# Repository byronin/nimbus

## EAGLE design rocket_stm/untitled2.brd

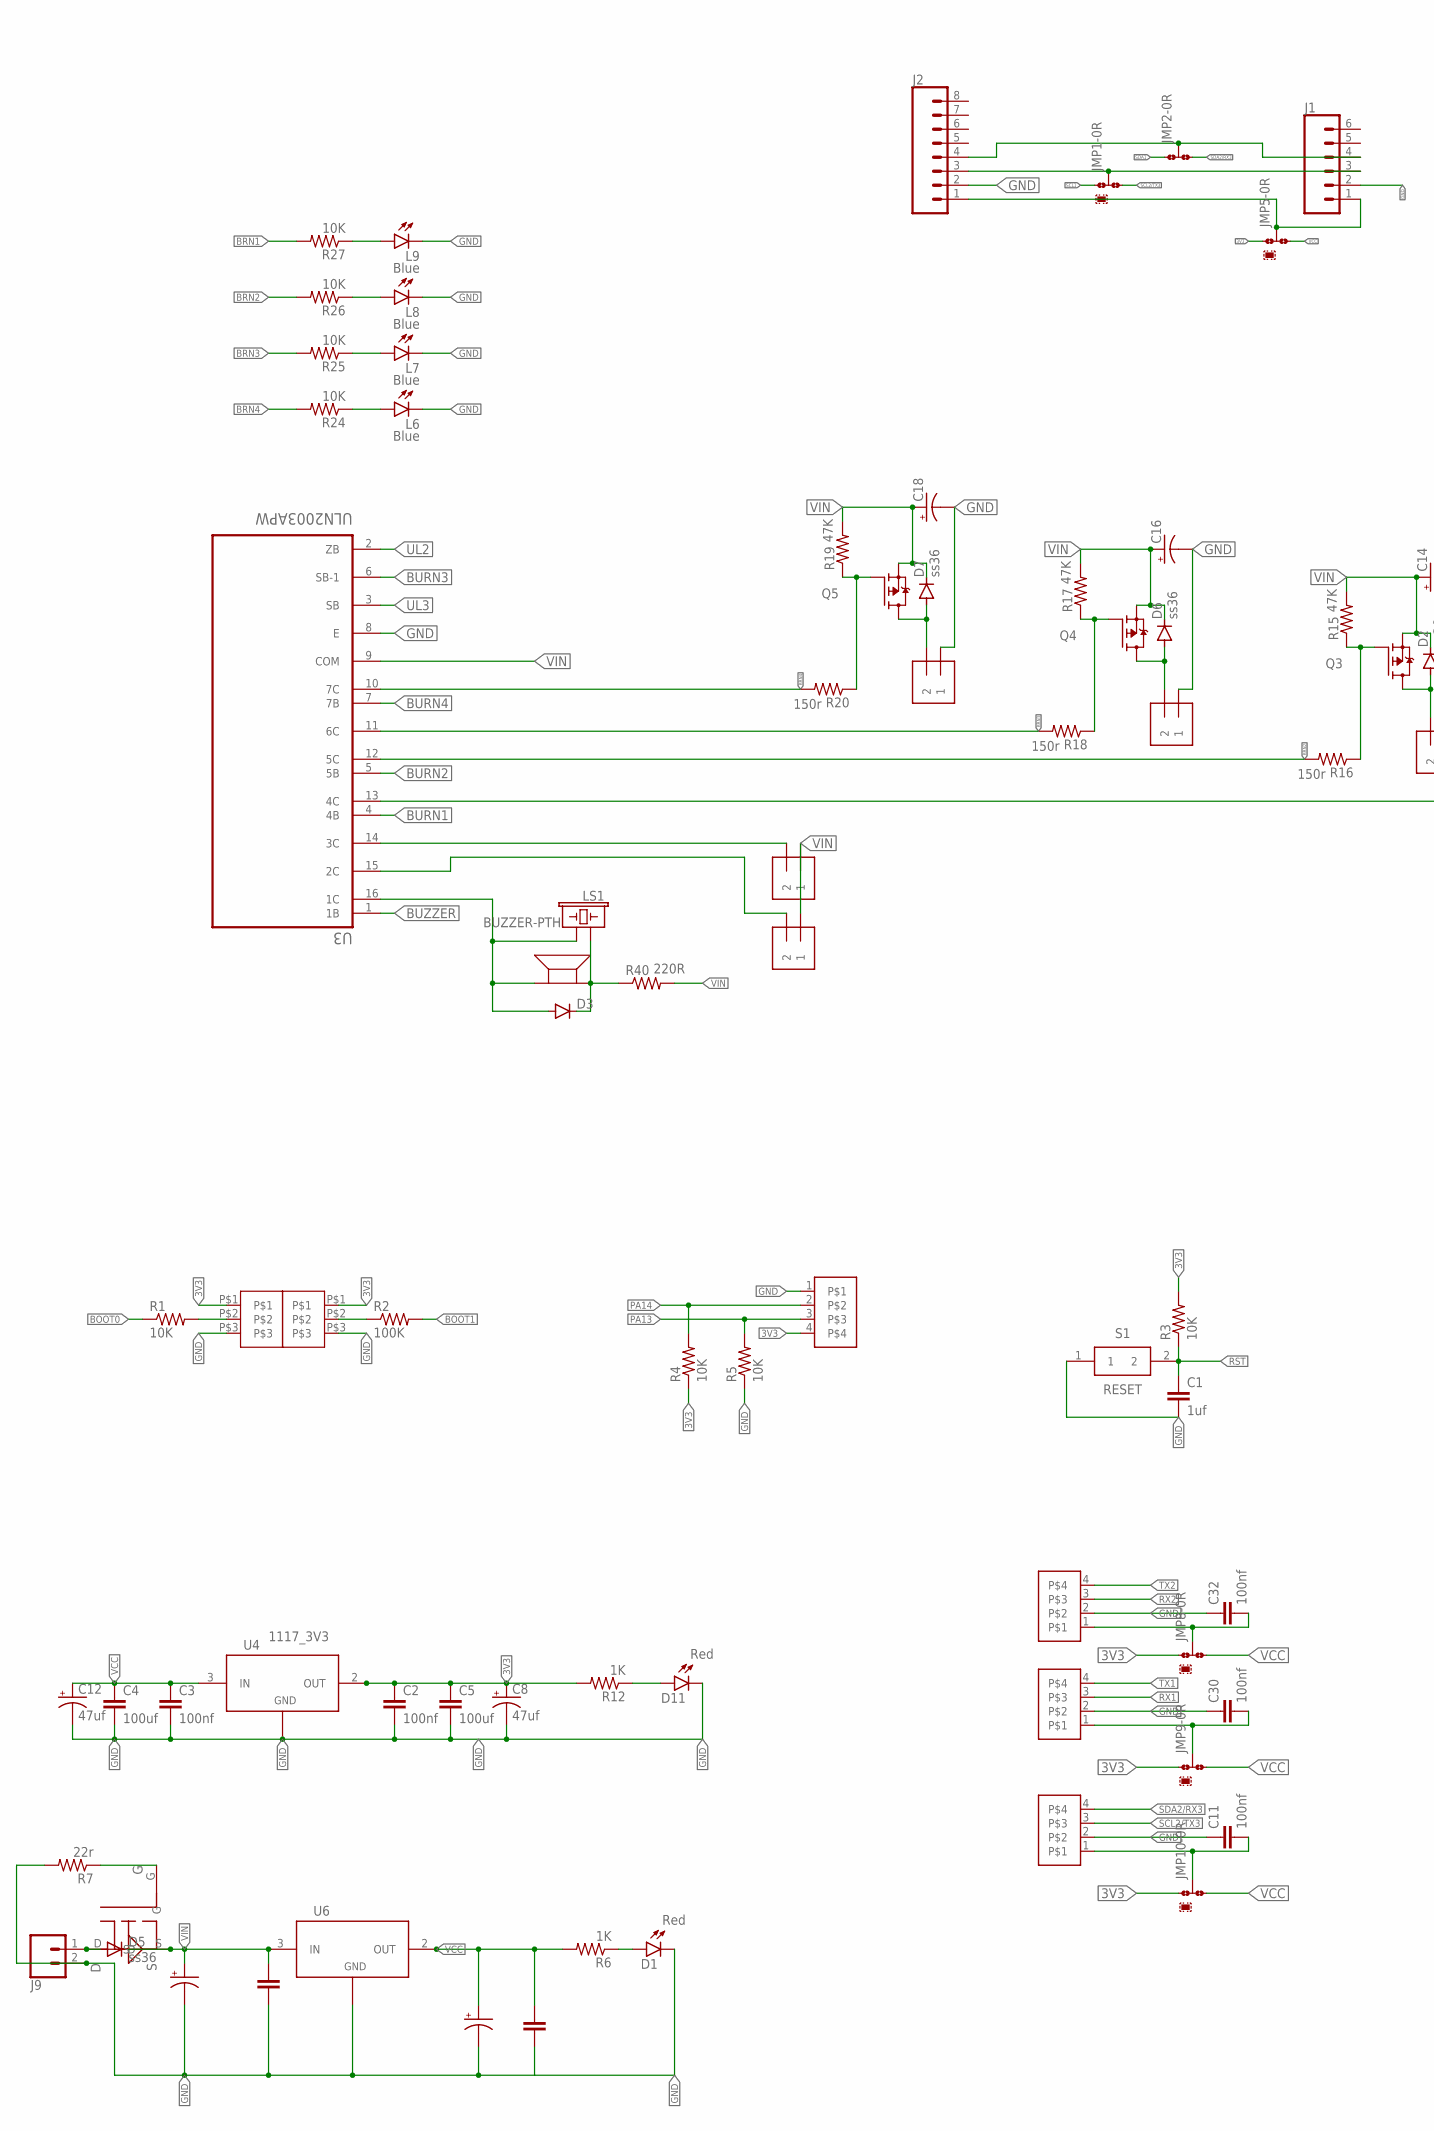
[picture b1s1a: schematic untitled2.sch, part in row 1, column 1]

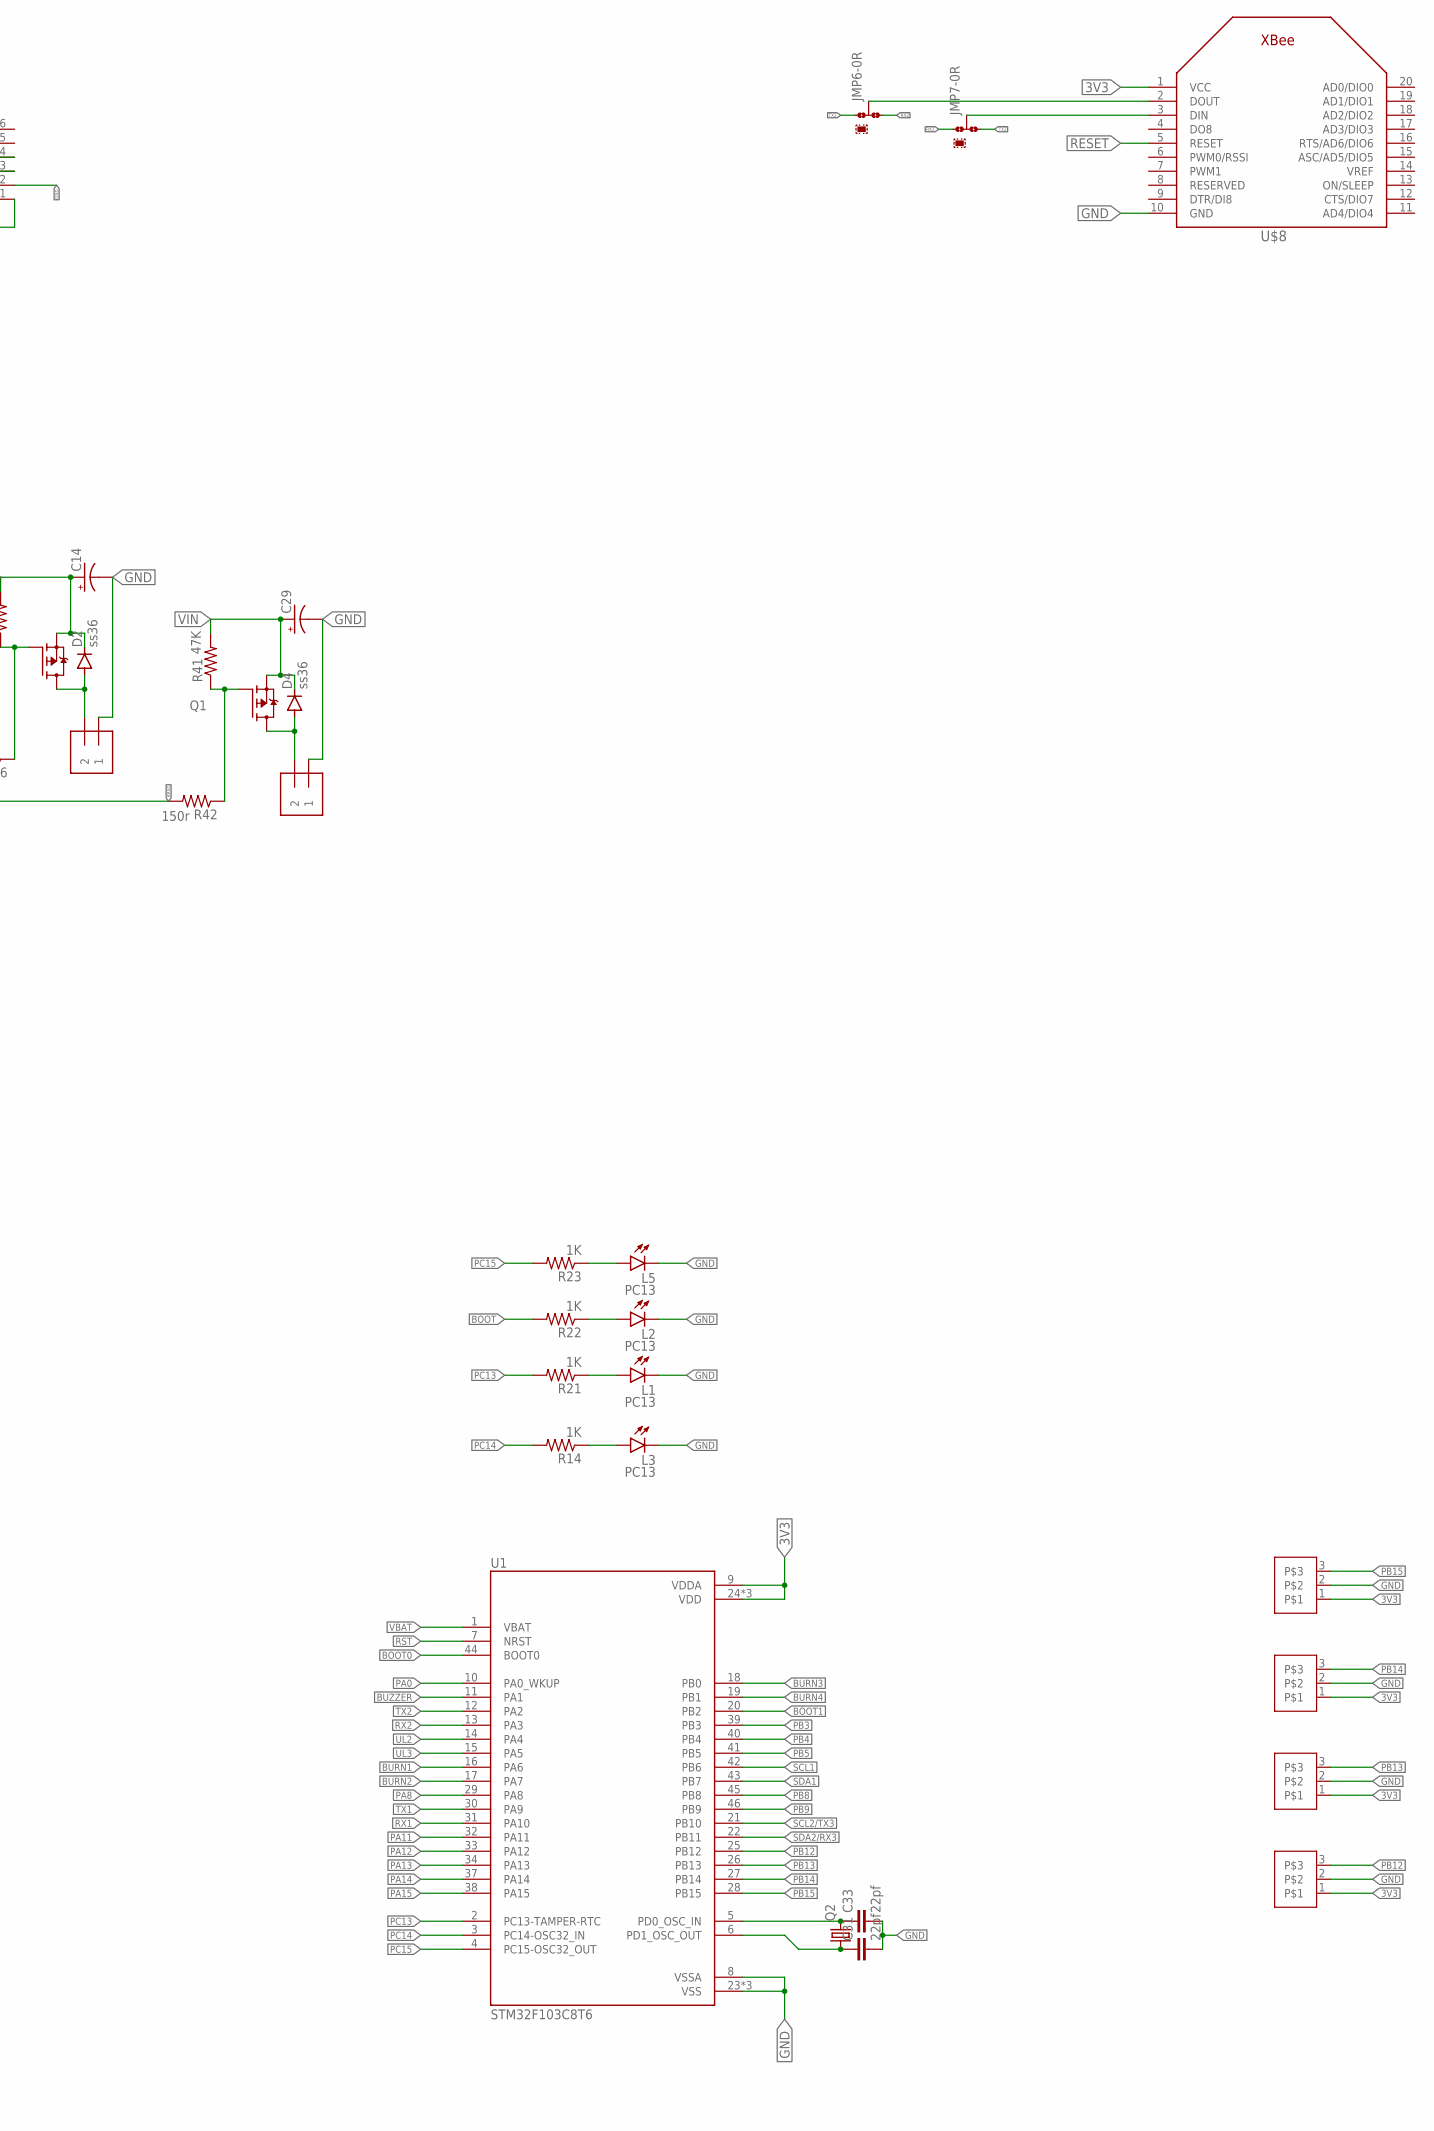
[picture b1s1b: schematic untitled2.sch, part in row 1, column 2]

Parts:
C1: 1uf; C0603
C2, C3, C6, C9, C11, C30, C32: 100nf; C0603
C4, C5: 100uf; C1210
C7, C10: 100uf; PANASONIC_D
C8, C12: 47uf; PANASONIC_C
C14, C16, C18, C29: CAPACITOR_POLC; PANASONIC_C
C31, C33: 22pf; C0603
D1, D11: Red; 0603_LED_GREEN
D2, D4, D5, D6, D7: ss36; DO-214AC
D3: DIODESOD; SOD-323
J1: CONN_06NO_SILK_NO_POP; 1X06_NO_SILK
J2: CONN_08NO_SILK_FEMALE_PTH; 1X08_NO_SILK
J9: CONN_025MM; SCREWTERMINAL-5MM-2
JMP1, JMP2, JMP5, JMP6, JMP7, JMP8, JMP9, JMP10: 0R-JUMPA; A0R-JMP
L1, L2, L3, L5: PC13; 0603_LED_GREEN
L6, L7, L8, L9: Blue; 0603_LED_GREEN
LS1: BUZZER-PTH; BUZZER-12MM
Q1, Q3, Q4, Q5: FDD4141TO252; TO252
Q2: CRYSTALHC49U-V; HC49U-V
Q6: AON7401; DFN-8_3X3
R1, R3, R4, R5, R24, R25, R26, R27: 10K; R0603
R2: 100K; R0603
R6, R12, R14, R21, R22, R23: 1K; R0603
R7: 22r; R0603
R15, R17, R19, R41: 47K; R0603
R16, R18, R20, R42: 150r; R0603
R40: 220R; R0603
S1: RESET; SKRK
U1: STM32F103C8T6; QFP50P900X900X160-48N
U3: ULN2003APW; SOP65P640X120-16N
U4, U6: 1117_3V3; SOT-223
U$1, U$2: FML_1X32MM; 1X3_2MM
U$3, U$7, U$11, U$12: FML_1X4; HDRVR4W64P254_1X4_1016X240X800B
U$4, U$5, U$6, U$20, U$21, U$22: 1X2
U$8: XBEE
U$9, U$13: Z_STOP; HDRVR3W64P254_1X3_762X240X800B
U$14: Y_STOP; HDRVR3W64P254_1X3_762X240X800B
U$15: X_STOP; HDRVR3W64P254_1X3_762X240X800B
U$19: 7.5X7.5_BUZZER; SMD_7.5_BUZZER

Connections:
3V3: C2.1, C5.1, C8.+, JMP5.1, JMP8.1, JMP9.1, JMP10.1, R3.2, R4.1, R12.2, U1.9 (VDDA), U1.24 (VDD), U1.36 (VDD), U1.48 (VDD), U4.2 (OUT), U4.4, U$1.P$1, U$2.P$1, U$3.4, U$8.1 (VCC), U$9.1, U$13.1, U$14.1, U$15.1
BOOT: R1.2, R22.2, U$2.P$2
BOOT0: R1.1, U1.44 (BOOT0)
BOOT1: R2.2, U1.20 (PB2)
BRN1: R27.2, R42.2, U3.13 (4C)
BRN2: R16.2, R26.2, U3.12 (5C)
BRN3: R18.2, R25.2, U3.11 (6C)
BRN4: R20.2, R24.2, U3.10 (7C)
BURN1: U1.16 (PA6), U3.4 (4B)
BURN2: U1.17 (PA7), U3.5 (5B)
BURN3: U1.18 (PB0), U3.6 (SB-1)
BURN4: U1.19 (PB1), U3.7 (7B)
BUZZER: U1.11 (PA1), U3.1 (1B)
GND: C1.2, C2.2, C3.2, C4.2, C5.2, C6.2, C7.-, C8.-, C9.2, C10.-, C11.1, C12.-, C14.-, C16.-, C18.-, C29.-, C30.1, C31.2, C32.1, C33.2, D1.C, D11.C, J1.2, J2.2, J9.2, L1.C, L2.C, L3.C, L5.C, L6.C, L7.C, L8.C, L9.C, R5.1, R7.2, S1.1, U1.8 (VSSA), U1.23 (VSS), U1.35 (VSS), U1.47 (VSS), U3.8 (E), U4.1 (ADJ/GND), U6.1 (ADJ/GND), U$1.P$3, U$2.P$3, U$3.1, U$4.P$1 (1), U$5.P$1 (1), U$6.P$1 (1), U$7.2, U$8.10 (GND), U$9.2, U$11.2, U$12.2, U$13.2, U$14.2, U$15.2, U$21.P$1 (1)
unnamed: Q6.G, R7.1
unnamed: R2.1, U$1.P$2
unnamed: D1.A, R6.1
unnamed: D11.A, R12.1
unnamed: JMP6.2, U$8.2 (DOUT)
unnamed: JMP7.2, U$8.3 (DIN)
unnamed: C30.2, JMP9.2, U$12.1
unnamed: L3.A, R14.1
unnamed: D2.A, Q3.3 (D), U$4.P$2 (2)
unnamed: Q3.1 (G), R15.1, R16.1
unnamed: D6.A, Q4.3 (D), U$5.P$2 (2)
unnamed: Q4.1 (G), R17.1, R18.1
unnamed: D7.A, Q5.3 (D), U$6.P$2 (2)
unnamed: Q5.1 (G), R19.1, R20.1
unnamed: C33.1, Q2.2, U1.5 (PD0_OSC_IN)
unnamed: C31.1, Q2.1, U1.6 (PD1_OSC_OUT)
unnamed: L1.A, R21.1
unnamed: L2.A, R22.1
unnamed: L5.A, R23.1
unnamed: L6.A, R24.1
unnamed: L7.A, R25.1
unnamed: L8.A, R26.1
unnamed: L9.A, R27.1
unnamed: C11.2, JMP10.2, U$7.1
unnamed: J1.1, J2.1, JMP5.2
unnamed: J1.3, J2.3, JMP1.2
unnamed: J1.4, J2.4, JMP2.2
unnamed: C32.2, JMP8.2, U$11.1
unnamed: D5.A, J9.1, Q6.D
unnamed: U3.15 (2C), U$20.P$2 (2)
unnamed: U3.14 (3C), U$22.P$2 (2)
unnamed: D3.A, LS1.- (2), U3.16 (1C), U$19.-
unnamed: D3.C, LS1.+ (1), R40.1, U$19.+
unnamed: D4.A, Q1.3 (D), U$21.P$2 (2)
unnamed: Q1.1 (G), R41.1, R42.1
PA0: U1.10 (PA0_WKUP)
PA8: U1.29 (PA8)
PA11: U1.32 (PA11)
PA12: U1.33 (PA12)
PA13: R5.2, U1.34 (PA13), U$3.3
PA14: R4.2, U1.37 (PA14), U$3.2
PA15: U1.38 (PA15)
PB3: U1.39 (PB3)
PB4: U1.40 (PB4)
PB5: U1.41 (PB5)
PB8: U1.45 (PB8)
PB9: U1.46 (PB9)
PB12: U1.25 (PB12), U$15.3
PB13: U1.26 (PB13), U$14.3
PB14: U1.27 (PB14), U$13.3
PB15: U1.28 (PB15), U$9.3
PC13: R21.2, U1.2 (PC13-TAMPER-RTC)
PC14: R14.2, U1.3 (PC14-OSC32_IN)
PC15: R23.2, U1.4 (PC15-OSC32_OUT)
RESET: U$8.5 (RESET)
RST: C1.1, R3.1, S1.2, U1.7 (NRST)
RX1: U1.31 (PA10), U$12.3
RX2: JMP6.3, JMP7.1, U1.13 (PA3), U$11.3
SCL1: JMP1.1, U1.42 (PB6)
SDA1: JMP2.1, U1.43 (PB7)
TX1: U1.30 (PA9), U$12.4
TX2: JMP6.1, JMP7.3, U1.12 (PA2), U$11.4
UL2: U1.14 (PA4), U3.2 (ZB)
UL3: U1.15 (PA5), U3.3 (SB)
VBAT: U1.1 (VBAT)
VCC: C3.1, C4.1, C6.1, C7.+, C12.+, JMP5.3, JMP8.3, JMP9.3, JMP10.3, R6.2, U4.3 (IN), U6.2 (OUT), U6.4
VIN: C9.1, C10.+, C14.+, C16.+, C18.+, C29.+, D2.C, D4.C, D5.C, D6.C, D7.C, Q1.2 (S), Q3.2 (S), Q4.2 (S), Q5.2 (S), Q6.S, R15.2, R17.2, R19.2, R40.2, R41.2, U3.9 (COM), U6.3 (IN), U$20.P$1 (1), U$22.P$1 (1)

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
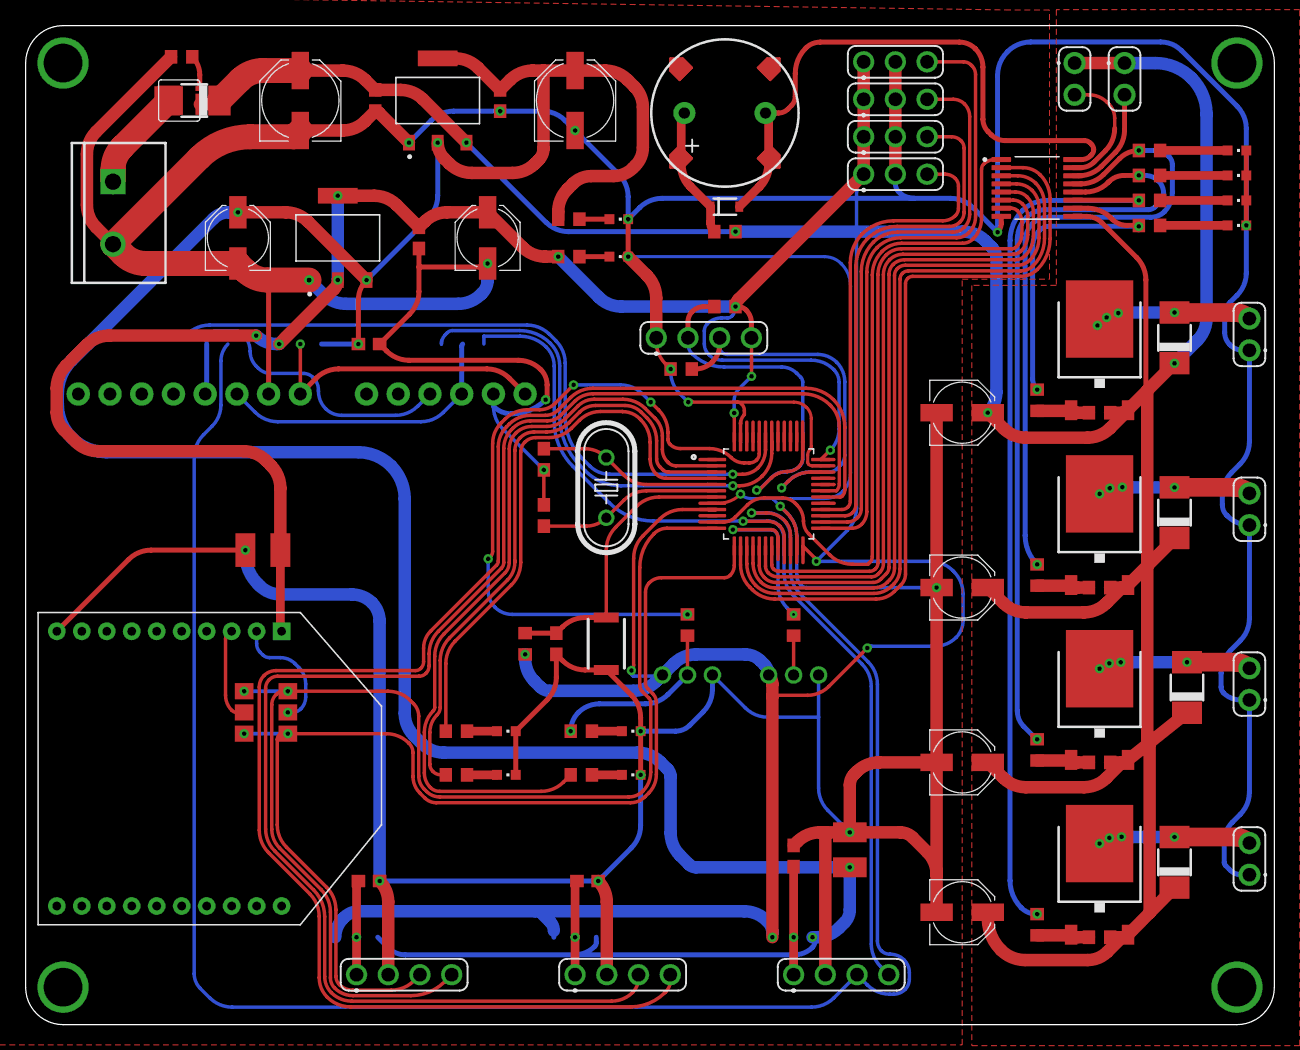
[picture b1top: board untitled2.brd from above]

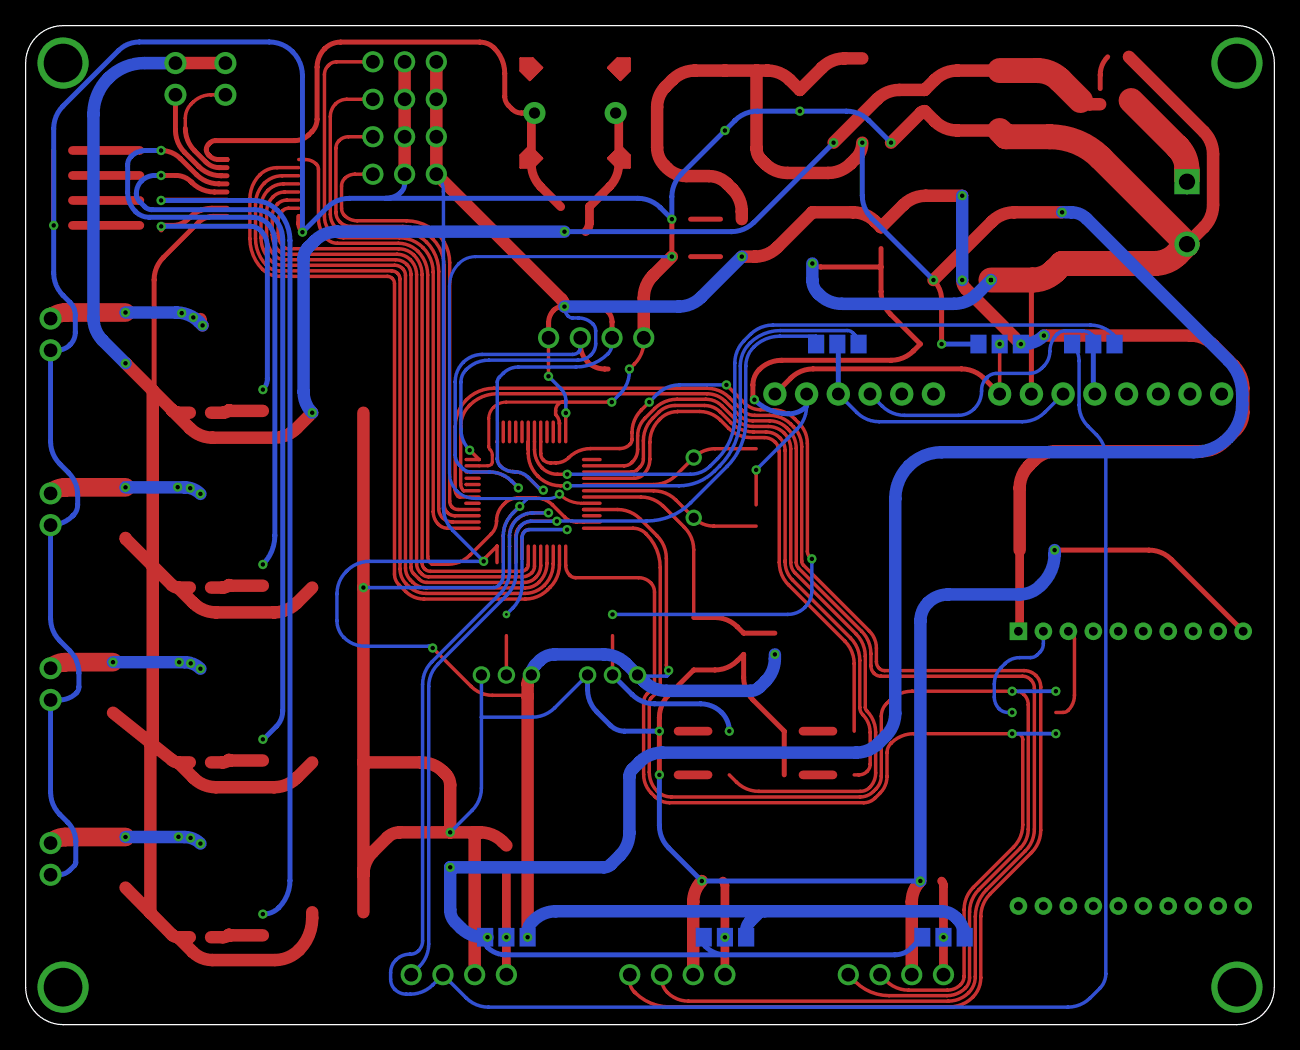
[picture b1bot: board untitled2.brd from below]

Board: 2 copper layers, 100.0 x 80.0 mm, 102 parts (6 on the bottom side), 71 nets.

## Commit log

2021-07-24 rtrn
2021-08-02 photo

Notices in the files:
parts and their libraries:
SparkFun-Connectors: Licensing: Creative Commons ShareAlike 4.0 International - https://creativecommons.org/licenses/by-sa/4.0
